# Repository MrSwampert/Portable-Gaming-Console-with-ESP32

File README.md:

# ArcadESP - The Open-Source Retro Gaming Handheld
Portable Gaming Console with ESP32-WROVER, TFT Display, and MicroSD Storage.

# Summary:

ArcadESP is an open-source, portable, retro video game console. Its main utility is to emulate games from classic consoles (such as the NES) using an ESP32 microcontroller, which is a very cheap and powerful chip. The main goal of the project is to leave it as a development board, which allows programming it for more functions.

# Description:
The circuit is centered on an ESP32-WROVER-IE microcontroller. The main power supply for the system is 3.3V.
The design integrates several key peripherals for operation. It includes a TFT screen for graphics display, managed through multiple GPIO connections of the microcontroller. For user input, the system features a series of buttons, including direction controls (up, down, left, right), action buttons (Start, Select, A, B, L, R), and menu buttons, which connect to a PCF8574 I/O port expander.
Data storage is handled through a MicroSD card slot with push-out functionality, allowing the reading and writing of information. Additionally, the circuit incorporates an auto-reset section for the microcontroller. Test points (TP1, TP2, TP3, TP4) are also included for monitoring key voltages such as V_USB, V_BATT and 3.3V.

# Features:
**Processing Core:** **ESP32-WROVER-IE** module with a dual-core CPU, Wi-Fi, Bluetooth, and integrated PSRAM.

**Connectivity & Power:** **USB-B port** for power and programming via an onboard **CH340 USB-to-UART** controller.

**Power Management:** Includes an **LTC4054** Li-Ion battery charger and an **MIC5219 LDO regulator** for a stable 3.3V supply.

**Audio Subsystem:** Features an I2S Stereo DAC (**UDA1334ATS**), a **PAM8403 Class-D amplifier**, and a **3.5mm audio jack** output.

**User Interface:** **TFT color display** for visual output, accompanied by user input buttons and a status LED.

**External Storage:** **Micro SD card slot** for expandable data and media storage.

**I/O Expansion:** **PCF8574 I/O expander** to provide additional digital pins over the I2C bus.

# Applications: 
-	Retro Emulation Console (Main Application)
-	Portable Media Player
-	IoT Device and Control Tool
-	Development and Learning Platform (All in One)

**Entertainment:** Play classic video games on a device you built yourself.
 
**Education:** It's a fantastic tool for learning about electronics, microcontroller programming (in the Arduino IDE), and how software emulation works.
 
**Personal Project (DIY):** It offers the satisfaction of building a functional gadget from scratch, with a very low cost (less than $20, according to similar projects).

# In Terms of Gaming:

Releases are here **https://github.com/retro-esp32/RetroESP32/releases**

It includes 11, YES eleven emulators.

 - Nintendo Entertainment System (NES)
 - Nintendo Game Boy (GB)
 - Nintendo Game Boy Color (GBC)
 - Sega Master System
 - Sega Game Gear
 - Colecovision
 - Sinclair Zx Spectrum 48k
 - Atari 2600
 - Atari 7800
 - Atari Lynx
 - PC Engine

# Sector Focus:
The project is clearly focused on the maker or DIY sector. The target audience are:
 
**Students and Electronics Hobbyists:** People who want to put their hardware and software knowledge into practice.

**Retro Gaming Enthusiasts:** Nostalgic gamers who would enjoy not only playing, but also building their own console.
 
**Programmers and Developers:** Those interested in developing software for embedded systems and optimizing code for hardware with limited resources. (For example, **PICO-8** is a virtual machine that emulates a video game console. While it is impossible to replicate with **ESP32**, there are alternatives such as **Fake-8**, which is the best open source way to run **PICO-8** games on unsupported platforms).

This is not a product for the end consumer looking for an **“out-of-the-box”** console, but for someone who values the process of creation and customization.

The differential value of ArcadESP is its low cost, the use of the versatile ESP32 and its open-source nature, which invites a community to modify, improve and share their own versions.

# Power Budget:

# Block Diagram:

# Schematic

# 3D Model:

# References:

Pebri, “GitHub - pebri86/esplay_micro_hardware: Micro version of esplay hardware, ESP32 based gaming console,” GitHub. **https://github.com/pebri86/esplay_micro_hardware**

“ESPLay Micro V2,” Handheld ESP32 Game Console | Makerfabs. **https://www.makerfabs.com/esplay-micro-v2.html** 

Pebri, “GitHub - pebri86/esplay-retro-emulation: Retro Emulation Collection for ESPlay Hardware, an ESP32 based game console,” GitHub. **https://github.com/pebri86/esplay-retro-emulation**

Pebri, “GitHub - pebri86/esplay-micro-firmware-collections: Firmware files collections (*.fw) for ESPlay Micro,” GitHub. **https://github.com/pebri86/esplay-micro-firmware-collections**

Jtothebell, “GitHub - jtothebell/fake-08: A Pico-8 player/emulator for console homebrew,” GitHub. **https://github.com/jtothebell/fake-08**

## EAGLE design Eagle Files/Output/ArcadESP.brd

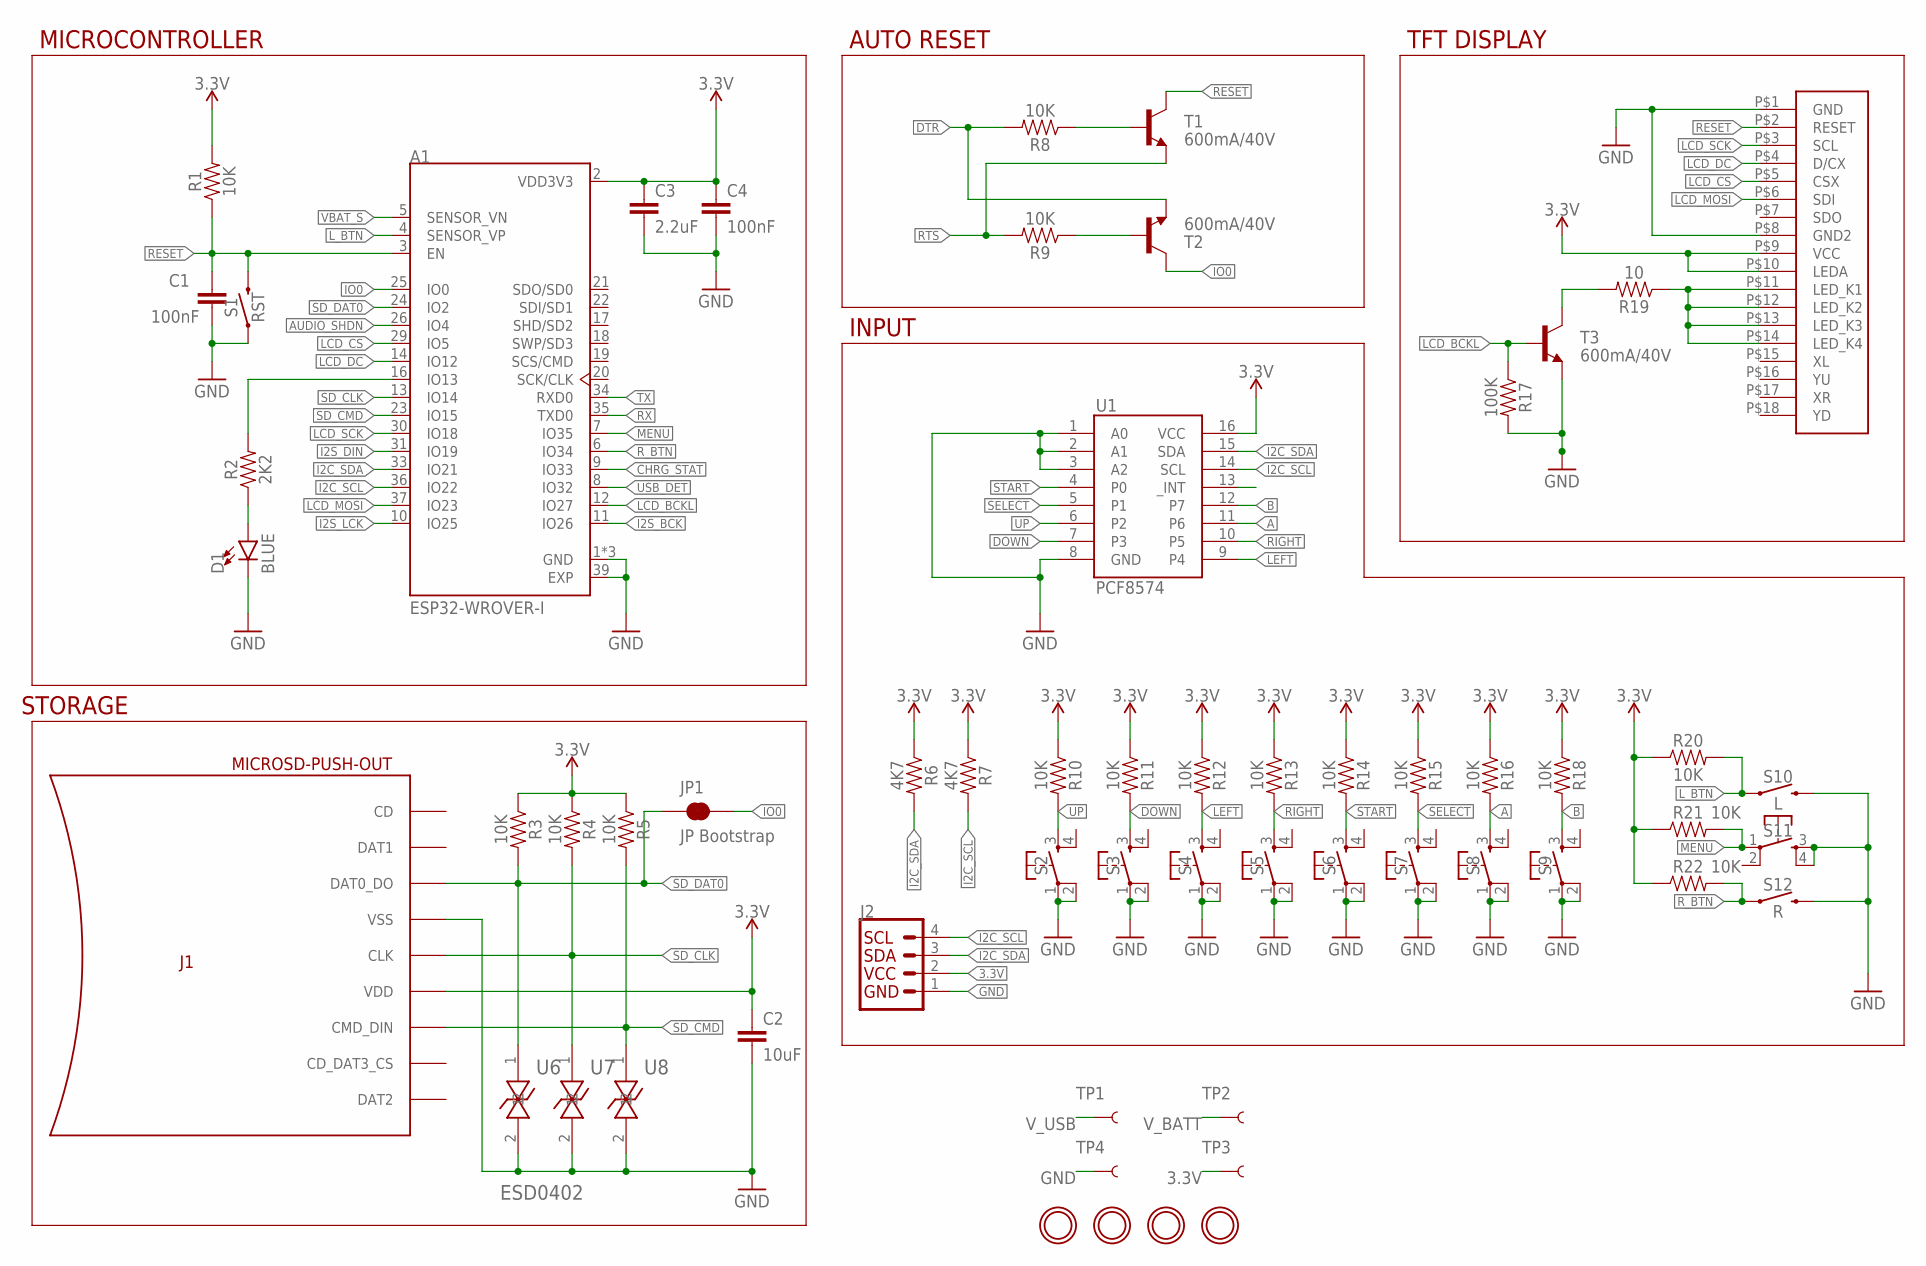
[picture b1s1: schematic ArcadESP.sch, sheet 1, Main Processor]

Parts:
A1: ESP32-WROVER-I; XCVR_ESP32-WROVER-I
C1, C4: 100nF; 0805
C2: 10uF; 0805
C3: 2.2uF; 0805
D1: BLUE; LED-0603
H1, H2, H3, H4: MICROBUILDER_MOUNTINGHOLE3.0THIN; MICROBUILDER_MOUNTINGHOLE_3.0_PLATEDTHIN
J1: MICROSD-PUSH-OUT
J2: QWIIC_CONNECTORJS-1MM; 1X04_1MM_RA
JP1: JP Bootstrap; SMT-JUMPER_2_NC_TRACE_NO-SILK
LCD1: ILI9341-2.4
R1, R3, R4, R5, R8, R9, R10, R11, R12, R13, R14, R15, R16, R18, R20, R21, R22: 10K; 0805
R2: 2K2; 0805
R6, R7: 4K7; 0805
R17: 100K; 0805
R19: 10; 0805
S1: RST; TACTILE_SWITCH_SMD_4.6X2.8MM
S2, S3, S4, S5, S6, S7, S8, S9, S11: MOMENTARY-SWITCH-SPST-2-SMD-5.2MM; TACTILE_SWITCH_SMD_5.2MM
S10: L; TACTILE_SWITCH_PTH_RIGHT_ANGLE_KIT
S12: R; TACTILE_SWITCH_PTH_RIGHT_ANGLE_KIT
T1, T2, T3: 600mA/40V; SOT23-3
TP1, TP2, TP3, TP4: TEST-POINT3; PAD.03X.03
U1: PCF8574; SO16
U6, U7, U8: ESD0402

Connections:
3.3V: A1.2 (VDD3V3), C2.1, C3.1, C4.1, J1.4 (VDD), J2.2, LCD1.P$9 (VCC), LCD1.P$10 (LEDA), R1.2, R3.1, R4.1, R5.1, R6.1, R7.1, R10.1, R11.1, R12.1, R13.1, R14.1, R15.1, R16.1, R18.1, R20.1, R21.1, R22.1, TP3.P$1, U1.16 (VCC); also elsewhere on the board
A: R16.2, S8.3, U1.11 (P6)
AUDIO_SHDN: A1.26 (IO4); also elsewhere on the board
B: R18.2, S9.3, U1.12 (P7)
CHRG_STAT: A1.9 (IO33); also elsewhere on the board
DOWN: R11.2, S3.3, U1.7 (P3)
DTR: R8.2, T2.2 (E); also elsewhere on the board
GND: A1.1 (GND), A1.15 (GND), A1.38 (GND), A1.39 (EXP), C1.2, C2.2, C3.2, C4.2, D1.C, J1.6 (VSS), J1.G1 (VSS), J1.G2 (VSS), J1.G3 (VSS), J1.G4 (VSS), J2.1, LCD1.P$1 (GND), LCD1.P$8 (GND2), R17.2, S1.1, S1.2 (1), S2.1, S2.2, S3.1, S3.2, S4.1, S4.2, S5.1, S5.2, S6.1, S6.2, S7.1, S7.2, S8.1, S8.2, S9.1, S9.2, S10.2, S11.3, S11.4, S12.2, T3.2 (E), TP4.P$1, U1.1 (A0), U1.2 (A1), U1.3 (A2), U1.8 (GND), U6.2, U7.2, U8.2; also elsewhere on the board
I2C_SCL: A1.36 (IO22), J2.4, R7.2, U1.14 (SCL)
I2C_SDA: A1.33 (IO21), J2.3, R6.2, U1.15 (SDA)
I2S_BCK: A1.11 (IO26); also elsewhere on the board
I2S_DIN: A1.31 (IO19); also elsewhere on the board
I2S_LCK: A1.10 (IO25); also elsewhere on the board
IO0: A1.25 (IO0), JP1.2, T2.3 (C)
LCD_BCKL: A1.12 (IO27), R17.1, T3.1 (B)
LCD_CS: A1.29 (IO5), LCD1.P$5 (CSX)
LCD_DC: A1.14 (IO12), LCD1.P$4 (D/CX)
LCD_MOSI: A1.37 (IO23), LCD1.P$6 (SDI)
LCD_SCK: A1.30 (IO18), LCD1.P$3 (SCL)
LEFT: R12.2, S4.3, U1.9 (P4)
L_BTN: A1.4 (SENSOR_VP), R20.2, S10.1
MENU: A1.7 (IO35), R21.2, S11.1
unnamed: A1.16 (IO13), R2.2
unnamed: D1.A, R2.1
unnamed: R19.2, T3.3 (C)
unnamed: LCD1.P$11 (LED_K1), LCD1.P$12 (LED_K2), LCD1.P$13 (LED_K3), LCD1.P$14 (LED_K4), R19.1
unnamed: R8.1, T1.1 (B)
unnamed: R9.1, T2.1 (B)
RESET: A1.3 (EN), C1.1, LCD1.P$2 (RESET), R1.1, S1.3 (2), S1.4 (2), T1.3 (C)
RIGHT: R13.2, S5.3, U1.10 (P5)
RTS: R9.2, T1.2 (E); also elsewhere on the board
RX: A1.35 (TXD0); also elsewhere on the board
R_BTN: A1.6 (IO34), R22.2, S12.1
SD_CLK: A1.13 (IO14), J1.5 (CLK), R4.2, U7.1
SD_CMD: A1.23 (IO15), J1.3 (CMD_DIN), R5.2, U8.1
SD_DAT0: A1.24 (IO2), J1.7 (DAT0_DO), JP1.1, R3.2, U6.1
SELECT: R15.2, S7.3, U1.5 (P1)
START: R14.2, S6.3, U1.4 (P0)
TX: A1.34 (RXD0); also elsewhere on the board
UP: R10.2, S2.3, U1.6 (P2)
USB_DET: A1.8 (IO32); also elsewhere on the board
VBAT_S: A1.5 (SENSOR_VN); also elsewhere on the board
V_BATT: TP2.P$1; also elsewhere on the board
V_USB: TP1.P$1; also elsewhere on the board

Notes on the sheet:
INPUT
TFT DISPLAY
AUTO RESET
STORAGE
MICROCONTROLLER

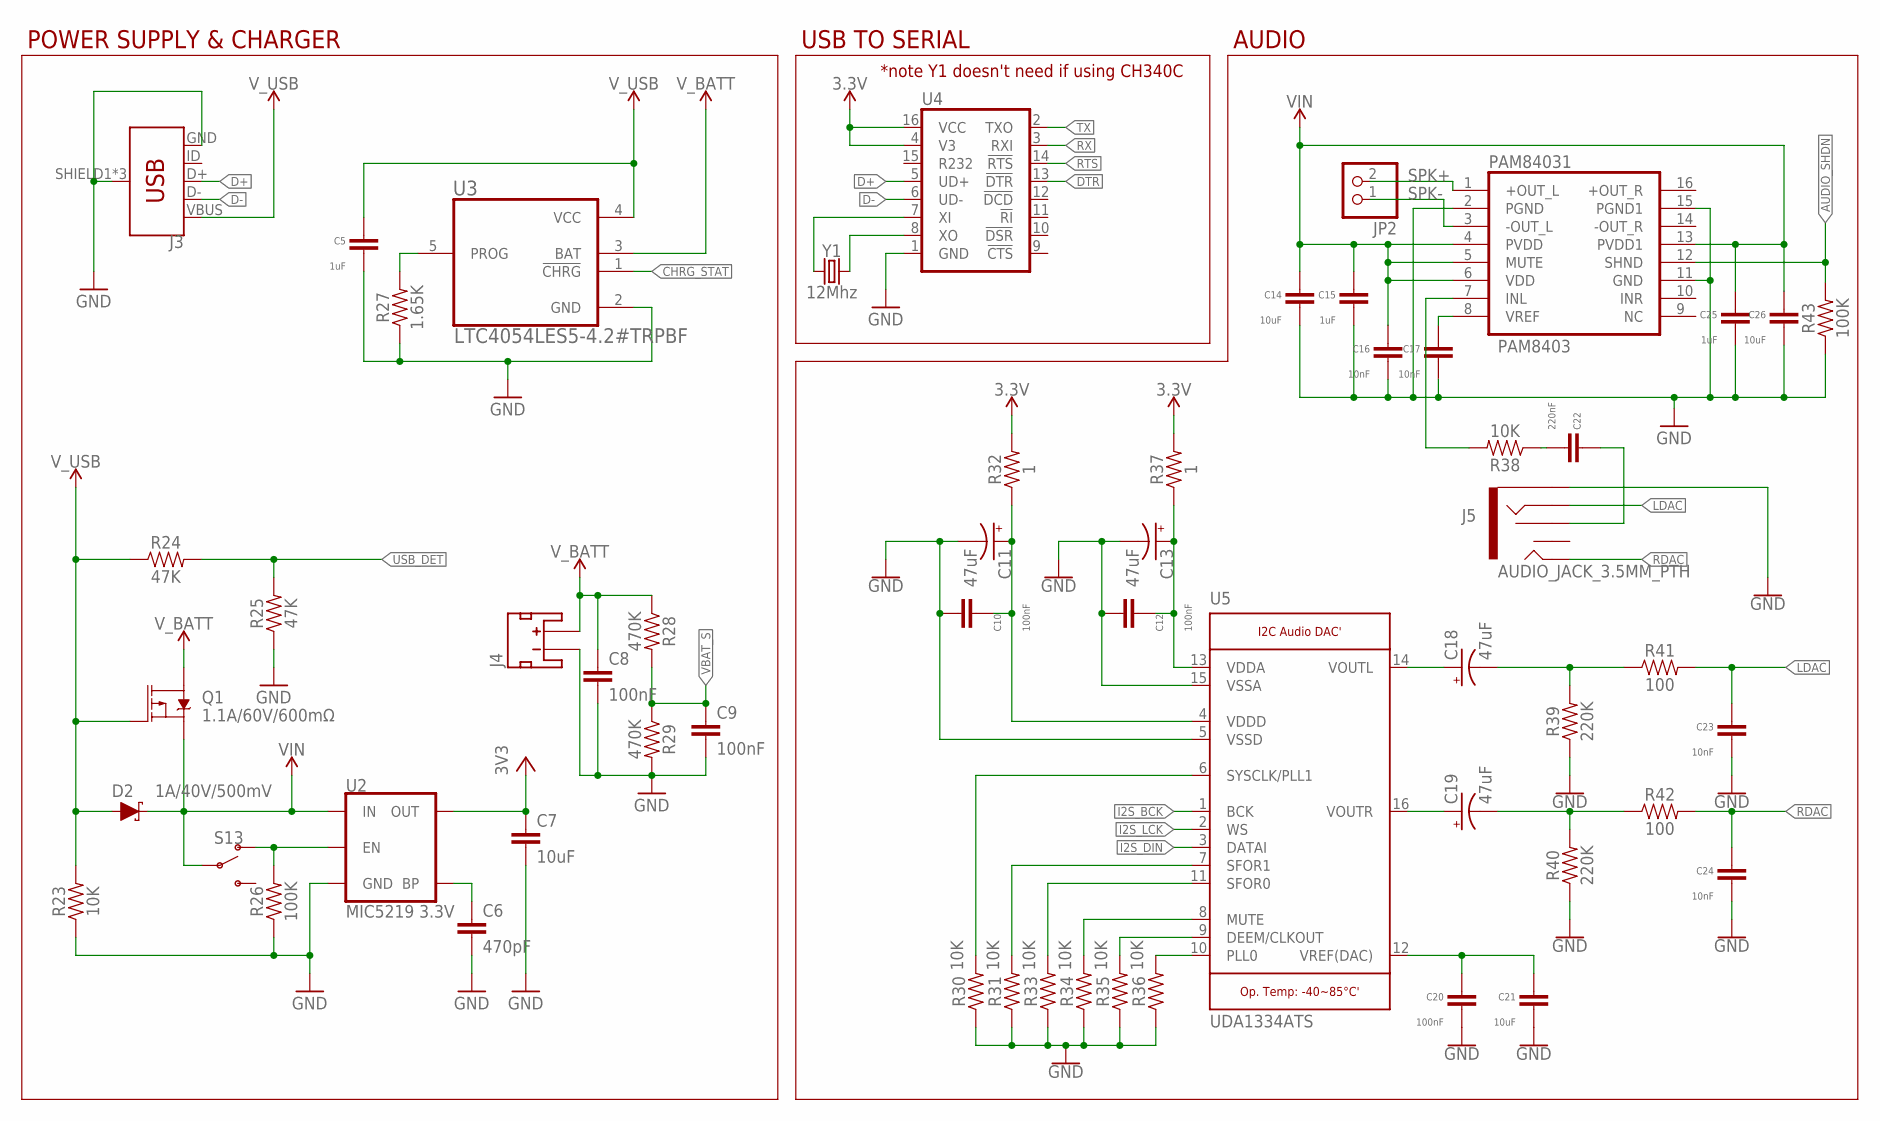
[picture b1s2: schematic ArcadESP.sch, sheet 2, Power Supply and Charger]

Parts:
C5, C15, C25: 1uF; 0805
C6: 470pF; 0805
C7, C14, C21, C26: 10uF; 0805
C8, C9, C10, C12, C20: 100nF; 0805
C11, C13, C18, C19: 47uF; EIA3528
C16, C17, C23, C24: 10nF; 0805
C22: 220nF; 0805
D2: 1A/40V/500mV; SMA-DIODE
J3: USB_MICRO-B_FEMALE-SMT; USB-B-MICRO-SMD
J4: JST_2MM_MALE; JST-2-SMD
J5: AUDIO_JACK_3.5MM_PTH; AUDIO-JACK
JP2: PINHD-1X2_2.00; 1X02M
PAM84031: PAM8403; SOP-16
Q1: 1.1A/60V/600mΩ; SOT23-3
R23, R30, R31, R33, R34, R35, R36, R38: 10K; 0805
R24, R25: 47K; 0805
R26, R43: 100K; 0805
R27: 1.65K; 0805
R28, R29: 470K; 0805
R32, R37: 1; 0805
R39, R40: 220K; 0805
R41, R42: 100; 0805
S13: SWITCH-SPDT-SMD-RIGHT-ANGLE; SWITCH_SPST_SMD_A
U2: MIC5219 3.3V; SOT23-5
U3: LTC4054LES5-4.2#TRPBF; SOT95P280X100-5N
U4: CH340G; SO016
U5: UDA1334ATS; MICROBUILDER_SSOP16_4.4MM
Y1: 12Mhz; CRYSTAL-SMD-5X3.2-4PAD

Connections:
3.3V: C7.1, R32.2, R37.2, U2.5 (OUT), U4.4 (V3), U4.16 (VCC); also elsewhere on the board
AUDIO_SHDN: PAM84031.12 (SHND), R43.2; also elsewhere on the board
CHRG_STAT: U3.1 (!CHRG); also elsewhere on the board
D+: J3.D+, U4.5 (UD+)
D-: J3.D-, U4.6 (UD-)
DTR: U4.13 (!DTR); also elsewhere on the board
GND: C5.1, C6.2, C7.2, C8.2, C9.2, C10.1, C11.C (-), C12.1, C13.C (-), C14.1, C15.1, C16.1, C17.1, C20.1, C21.1, C23.1, C24.1, C25.1, C26.1, J3.GND, J3.SHIELD1 (SHIELD), J3.SHIELD2 (SHIELD), J3.SHIELD3 (SHIELD), J4.1 (-), J5.SLEEVE, PAM84031.2 (PGND), PAM84031.11 (GND), PAM84031.15 (PGND1), R23.1, R25.1, R26.1, R27.1, R29.2, R30.1, R31.1, R33.1, R34.1, R35.1, R36.1, R39.1, R40.1, R43.1, U2.2 (GND), U3.2 (GND), U4.1 (GND), U5.5 (VSSD), U5.15 (VSSA); also elsewhere on the board
I2S_BCK: U5.1 (BCK); also elsewhere on the board
I2S_DIN: U5.3 (DATAI); also elsewhere on the board
I2S_LCK: U5.2 (WS); also elsewhere on the board
LDAC: C23.2, J5.RING, R41.2
unnamed: R27.2, U3.5 (PROG)
unnamed: U4.7 (XI), Y1.3 (2)
unnamed: C18.A (+), U5.14 (VOUTL)
unnamed: U4.8 (XO), Y1.1
unnamed: R26.2, S13.1 (O), U2.3 (EN)
unnamed: C6.1, U2.4 (BP)
unnamed: C19.A (+), U5.16 (VOUTR)
unnamed: C17.2, PAM84031.8 (VREF)
unnamed: PAM84031.7 (INL), R38.2
unnamed: C18.C (-), R39.2, R41.1
unnamed: C19.C (-), R40.2, R42.1
unnamed: C12.2, C13.A (+), R37.1, U5.13 (VDDA)
unnamed: C20.2, C21.2, U5.12 (VREF(DAC))
unnamed: C10.2, C11.A (+), R32.1, U5.4 (VDDD)
unnamed: C22.1, R38.1
unnamed: R30.2, U5.6 (SYSCLK/PLL1)
unnamed: R31.2, U5.7 (SFOR1)
unnamed: R33.2, U5.11 (SFOR0)
unnamed: R34.2, U5.8 (MUTE)
unnamed: R35.2, U5.9 (DEEM/CLKOUT)
unnamed: R36.2, U5.10 (PLL0)
unnamed: C22.2, J5.RSH
RDAC: C24.2, J5.TIP, R42.2
RTS: U4.14 (!RTS); also elsewhere on the board
RX: U4.3 (RXI); also elsewhere on the board
SPK+: JP2.2, PAM84031.1 (+OUT_L)
SPK-: JP2.1, PAM84031.3 (-OUT_L)
TX: U4.2 (TXO); also elsewhere on the board
USB_DET: R24.2, R25.2; also elsewhere on the board
VBAT_S: C9.1, R28.2, R29.1; also elsewhere on the board
VIN: C14.2, C15.2, C16.2, C25.2, C26.2, D2.C, PAM84031.4 (PVDD), PAM84031.5 (MUTE), PAM84031.6 (VDD), PAM84031.13 (PVDD1), Q1.2 (S), S13.2, U2.1 (IN)
V_BATT: C8.1, J4.2 (+), Q1.3 (D), R28.1, U3.3 (BAT); also elsewhere on the board
V_USB: C5.2, D2.A, J3.VBUS, Q1.1 (G), R23.2, R24.1, U3.4 (VCC); also elsewhere on the board

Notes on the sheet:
POWER SUPPLY & CHARGER
USB TO SERIAL
AUDIO
*note Y1 doesn't need if using CH340C

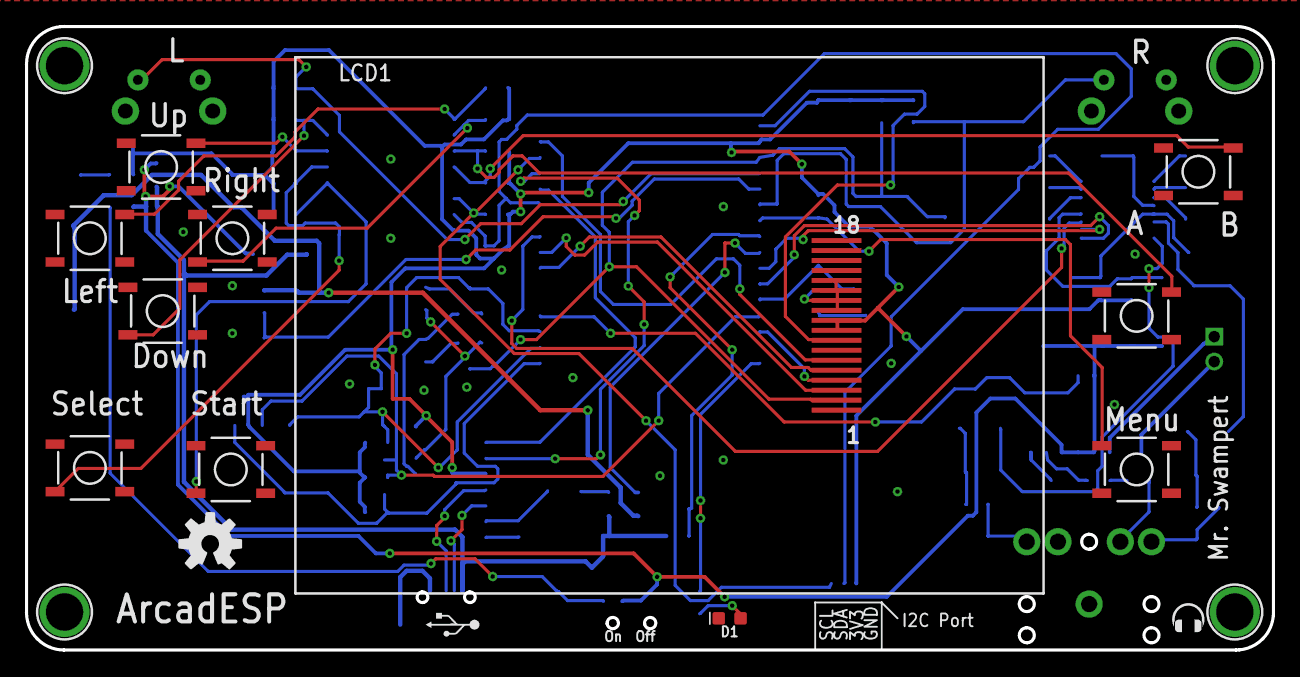
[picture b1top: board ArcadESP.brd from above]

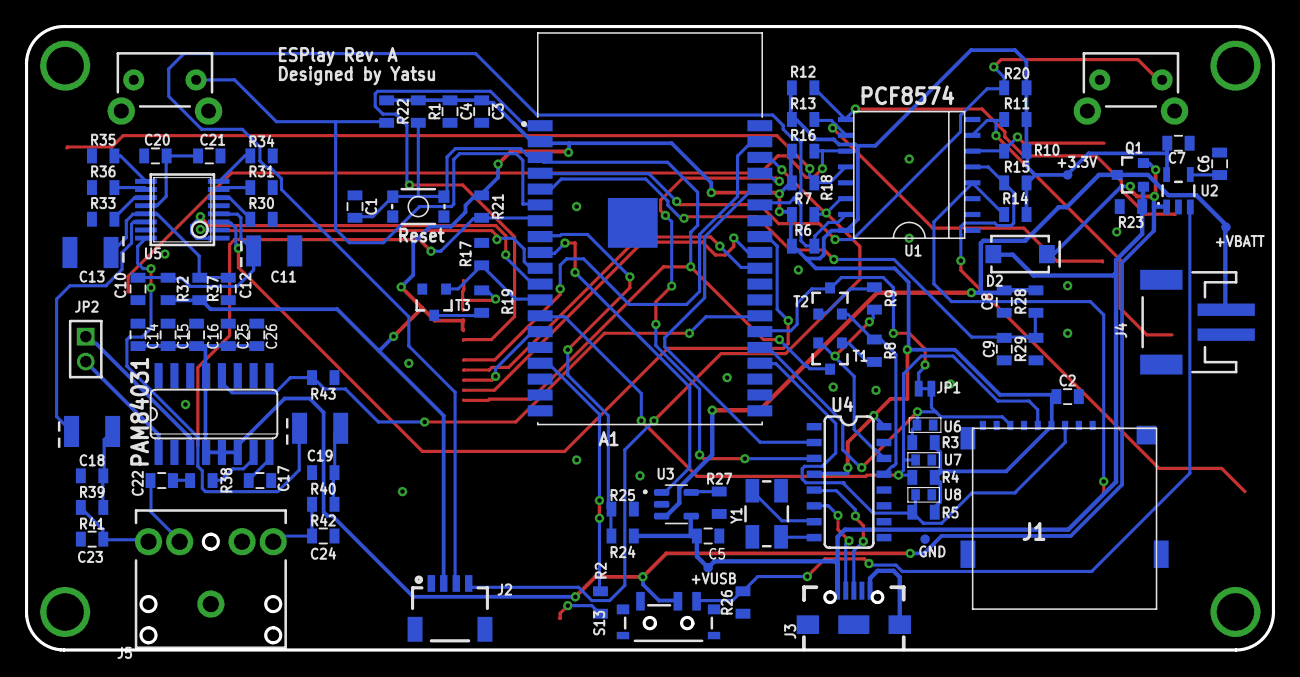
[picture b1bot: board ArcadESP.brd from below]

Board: 2 copper layers, 100.0 x 50.0 mm, 118 parts (100 on the bottom side), 73 nets.

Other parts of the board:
U$1: OSHW-LOGO-M
U$2: USB_LOGO
U$3: HEADPHONE_LOGO

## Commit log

2025-07-09 Update README.md
    Se añaden apuntes con información valiosa
2025-07-09 Upload Docs
    Se añade documentos
2025-07-10 Update README.md
    Upload README
2025-07-14 Add Report Components
    Se añade un informe analizado con IA de algunos cambios al proyecto original
2025-07-14 Add BOM
    Se añade la lista de los materiales con sus enlaces respectivos
2025-07-15 Upload Files
    Se añaden nuevos documentos, incluido el BOM el cual le hace falta buscar unos componentes
2025-07-15 Update Upload
    Se añade imagen de la PCB en 3D
2025-07-15 Upload BOM
    Se actualiza el BOM con el subtotal de todo, pero siguen faltando componentes por buscar
2025-07-22 Update README.md
    Add New Information
2025-07-22 Update README.md
    Change References
2025-07-22 Upload Files
    Add New Files
2025-07-22 Add New Folder
    Add New Folder
2025-07-22 Add Eagle Folder
    Add Eagle Folder with Output Files
2025-07-22 Update README.md
    Update Power Budget
2025-07-22 Add New Files
    Add Power Budget and Block Diagram
2025-07-22 Add New Files
    Add docx and pdf
2025-07-22 Update README.md
    Add Gaming Info
2025-07-22 Update README.md
    Update Gaming Info
2025-07-22 Update README.md
    Add New References
2025-07-22 Update README.md
    Update Features
2025-07-22 Update README.md
    Update Features again
2025-07-22 Update README.md
    Change 3D Model
2025-07-22 Add new files
    Upload docx and pdf
2025-07-23 Add schematics
    Add old and new version
2025-07-23 Update schematic
    Add new version v2
2025-07-23 Update README.md
    Add new sections
2025-07-23 Add schematic
    Add new version v3
2025-07-23 Update README.md
    Replace schematic pag 2
2025-07-24 Add docs
2025-07-24 Add Imported File
2025-07-24 Add Altium Files
    Add Altium Files

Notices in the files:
parts and their libraries:
SparkFun-Capacitors: Licensing: Creative Commons ShareAlike 4.0 International - https://creativecommons.org/licenses/by-sa/4.0
